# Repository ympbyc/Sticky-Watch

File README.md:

ISD1700 Fragmented Memory Manager
=================================

Arduino sketch that controls ISD1700 record/playback ic over SPI. It's packed with awesome features. Read on.

<!--  -->

Caution
-------

It's a WIP and a little buggy.

Features
--------

+ Fragmented memory management: divides the memory into N fixed-size randomly-accessible sections.
+ LED indicators: N LEDs can be attached to IO pins to indicate memory occupancy status and cursor position.
+ Multi-function buttons: Reduce the number of pushbuttons by utilizing single-click/double-click/long-press actions.
+ Sleep mode: Arduino enters SLEEP_MODE_PWR_DOWN after putting ISD1700 to power-down mode. Wakes up on button action and immediately executes the given command.

\* N being an integer

Default Setup
-------------

### Memory management

Address range is configured for ISD1790. Adjust LAST_ADDR macro value to match your chip. (Refer to ISD1700 Design Guide)

Number of sections the memory gets devided into is set by SLOT_NUM macro.

### APC register

By default the APC is setup to accept input from Mic. Change the APC macro value to match your need. (Refer to ISD1700 Design Guide)

### Push Buttons

#### MAIN_BTN

+ single-click: (play) play current section
+ long-press:   (rec)  start recording into first vacant section

#### SUB_BTN

+ single-click: forward
+ long-press:   erase current slot

### LEDs

+ ON when the section is occupied
+ OFF when the section is vacant
+ Blink to indicate current section (play, fwd, rec)

Default Wiring
--------------

| ISD1700 | Arduino |
| ------- | ------- |
| MISO    | D12     |
| MOSI    | D11     |
| SCLK    | D13     |
| SS      | D10     |

| Arduino | LED/BTN  |
| ------- | -------- |
| D14(A0) | LED0     |
| D15(A1) | LED1     |
| ...     | LEDN-1   |
| D3      | MAIN_BTN |
| D2      | SUB_BTN  |

Schematic
---------

<!--  -->

<!--  -->

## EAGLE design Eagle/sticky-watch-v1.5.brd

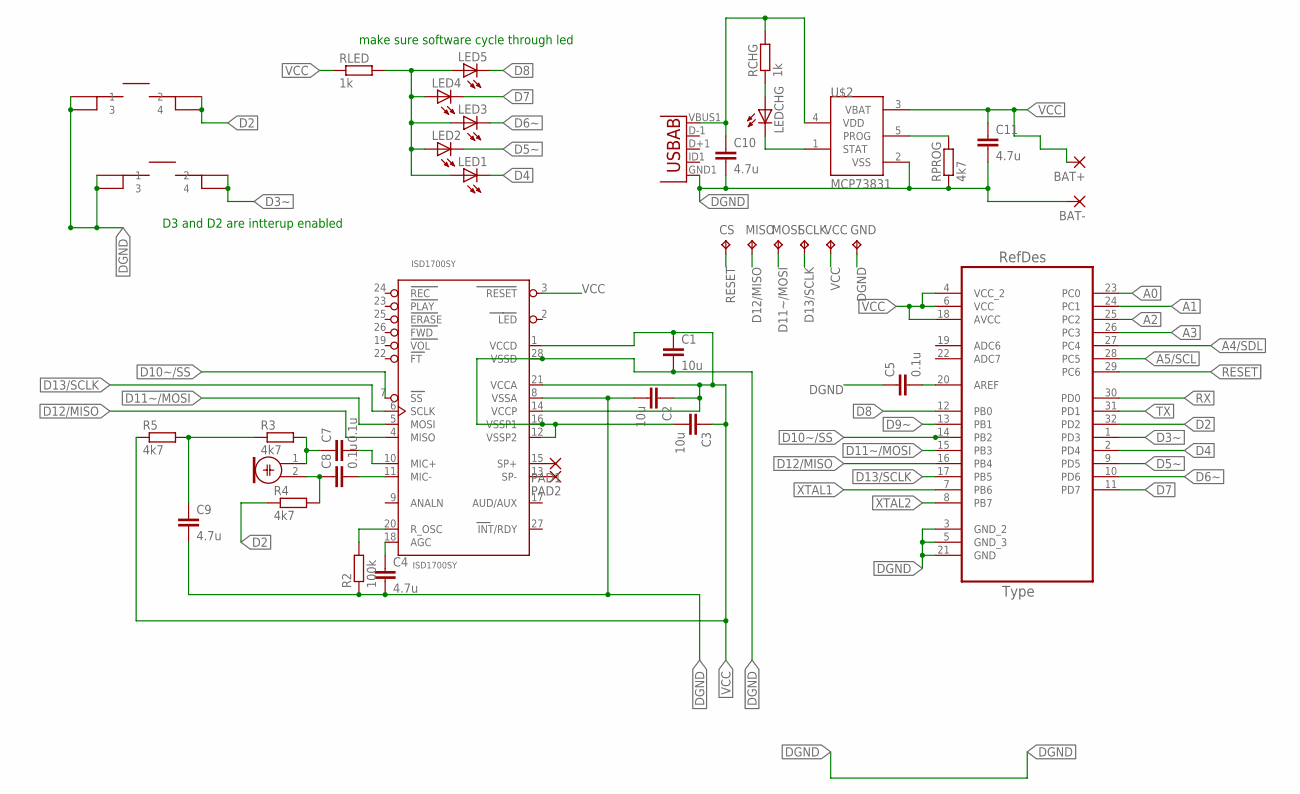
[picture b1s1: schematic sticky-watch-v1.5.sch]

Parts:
BAT+: 1,6/0,8
BAT-: 1,6/0,8
C1, C2, C3: 10u; C0603
C4, C9, C10, C11: 4.7u; C0603
C5, C7, C8: 0.1u; C0603
CS: TPTP10R; TP10R
GND: TPTP10R; TP10R
ISD1700SY: ISD1700SY; SO28W
LED1, LED2, LED3, LED4, LED5: LEDSML0805; SML0805
LEDCHG: LEDSML0805; SML0805
M1: ELECTRET_MICROPHON-WM-63PR; WM-63PR
MISO: TPTP10R; TP10R
MOSI: TPTP10R; TP10R
PAD1, PAD2: 1,6/0,8
R2: 100k; R0603
R3, R4, R5: 4k7; R0603
RCHG: 1k; R0603
RLED: 1k; R0603
RPROG: 4k7; R0603
S1: 0; SMD-TACT-5.2MM
S2: SMD-TACT; SMD-TACT-5.2MM
SCLK: TPTP10R; TP10R
U1: ATMEGA328P-AU; QFP80P900X900X120-32N
U2: USB""; USB-MICRO-SMD
U$2: MCP73831; SOT23-5L
VCC: TPTP10R; TP10R

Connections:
A0: U1.23 (PC0)
A1: U1.24 (PC1)
A2: U1.25 (PC2)
A3: U1.26 (PC3)
A4/SDL: U1.27 (PC4)
A5/SCL: U1.28 (PC5)
D2: R4.1, S2.2, S2.4, U1.32 (PD2)
D3~: S1.2, S1.4, U1.1 (PD3)
D4: LED1.C, U1.2 (PD4)
D5~: LED2.C, U1.9 (PD5)
D6~: LED3.C, U1.10 (PD6)
D7: LED4.C, U1.11 (PD7)
D8: LED5.C, U1.12 (PB0)
D9~: U1.13 (PB1)
D10~/SS: ISD1700SY.7 (SS), U1.14 (PB2)
D11~/MOSI: ISD1700SY.5 (MOSI), MOSI.TP, U1.15 (PB3)
D12/MISO: ISD1700SY.4 (MISO), MISO.TP, U1.16 (PB4)
D13/SCLK: ISD1700SY.6 (SCLK), SCLK.TP, U1.17 (PB5)
DGND: BAT-.1, C1.2, C2.2, C3.2, C4.2, C5.1, C9.2, C10.2, C11.2, GND.TP, ISD1700SY.8 (VSSA), ISD1700SY.12 (VSSP2), ISD1700SY.16 (VSSP1), ISD1700SY.28 (VSSD), R2.1, RPROG.1, S1.1, S1.3, S2.1, S2.3, U1.3 (GND_2), U1.5 (GND_3), U1.21 (GND), U2.GND1 (GND), U$2.2 (VSS)
unnamed: LED1.A, LED2.A, LED3.A, LED4.A, LED5.A, RLED.2
unnamed: C10.1, RCHG.2, U2.VBUS1 (VBUS), U$2.4 (VDD)
unnamed: ISD1700SY.15 (SP+), PAD1.1
unnamed: LEDCHG.A, RCHG.1
unnamed: C7.2, ISD1700SY.10 (MIC+)
unnamed: LEDCHG.C, U$2.1 (STAT)
unnamed: C5.2, U1.20 (AREF)
unnamed: ISD1700SY.13 (SP-), PAD2.1
unnamed: C4.1, ISD1700SY.18 (AGC)
unnamed: ISD1700SY.20 (R_OSC), R2.2
unnamed: C8.2, ISD1700SY.11 (MIC-)
unnamed: C8.1, M1.2, R4.2
unnamed: RPROG.2, U$2.5 (PROG)
unnamed: C9.1, R3.1, R5.2
unnamed: C7.1, M1.1, R3.2
RESET: CS.TP, U1.29 (PC6)
RX: U1.30 (PD0)
TX: U1.31 (PD1)
VCC: BAT+.1, C1.1, C2.1, C3.1, C11.1, ISD1700SY.1 (VCCD), ISD1700SY.3 (RESET), ISD1700SY.14 (VCCP), ISD1700SY.21 (VCCA), R5.1, RLED.1, U1.4 (VCC_2), U1.6 (VCC), U1.18 (AVCC), U$2.3 (VBAT), VCC.TP
XTAL1: U1.7 (PB6)
XTAL2: U1.8 (PB7)

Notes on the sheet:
make sure software cycle through led
D3 and D2 are intterup enabled

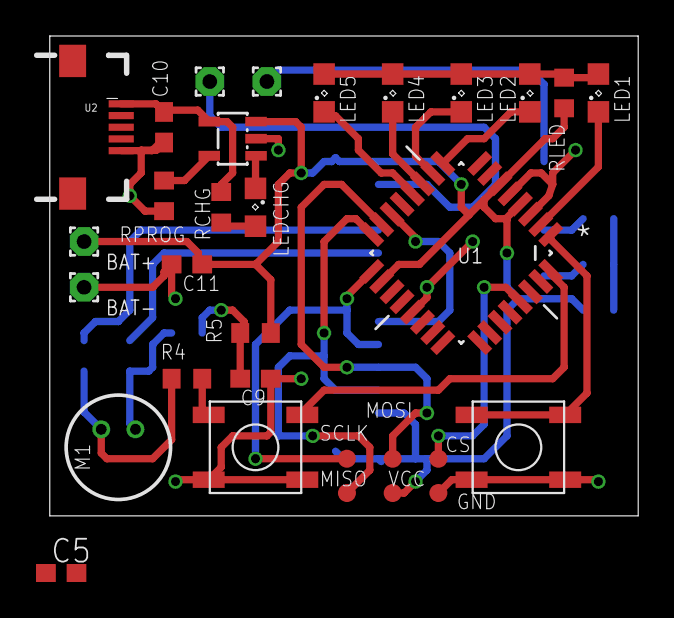
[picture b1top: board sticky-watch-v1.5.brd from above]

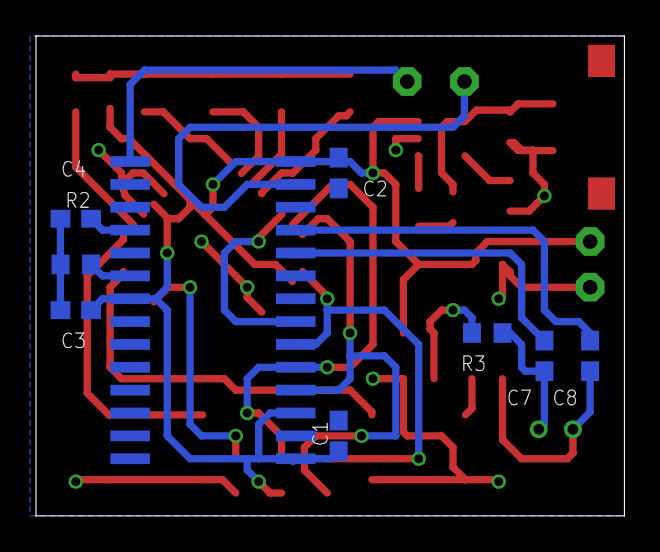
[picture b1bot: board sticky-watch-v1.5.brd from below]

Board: 2 copper layers, 32.7 x 26.7 mm, 40 parts (9 on the bottom side), 29 nets.

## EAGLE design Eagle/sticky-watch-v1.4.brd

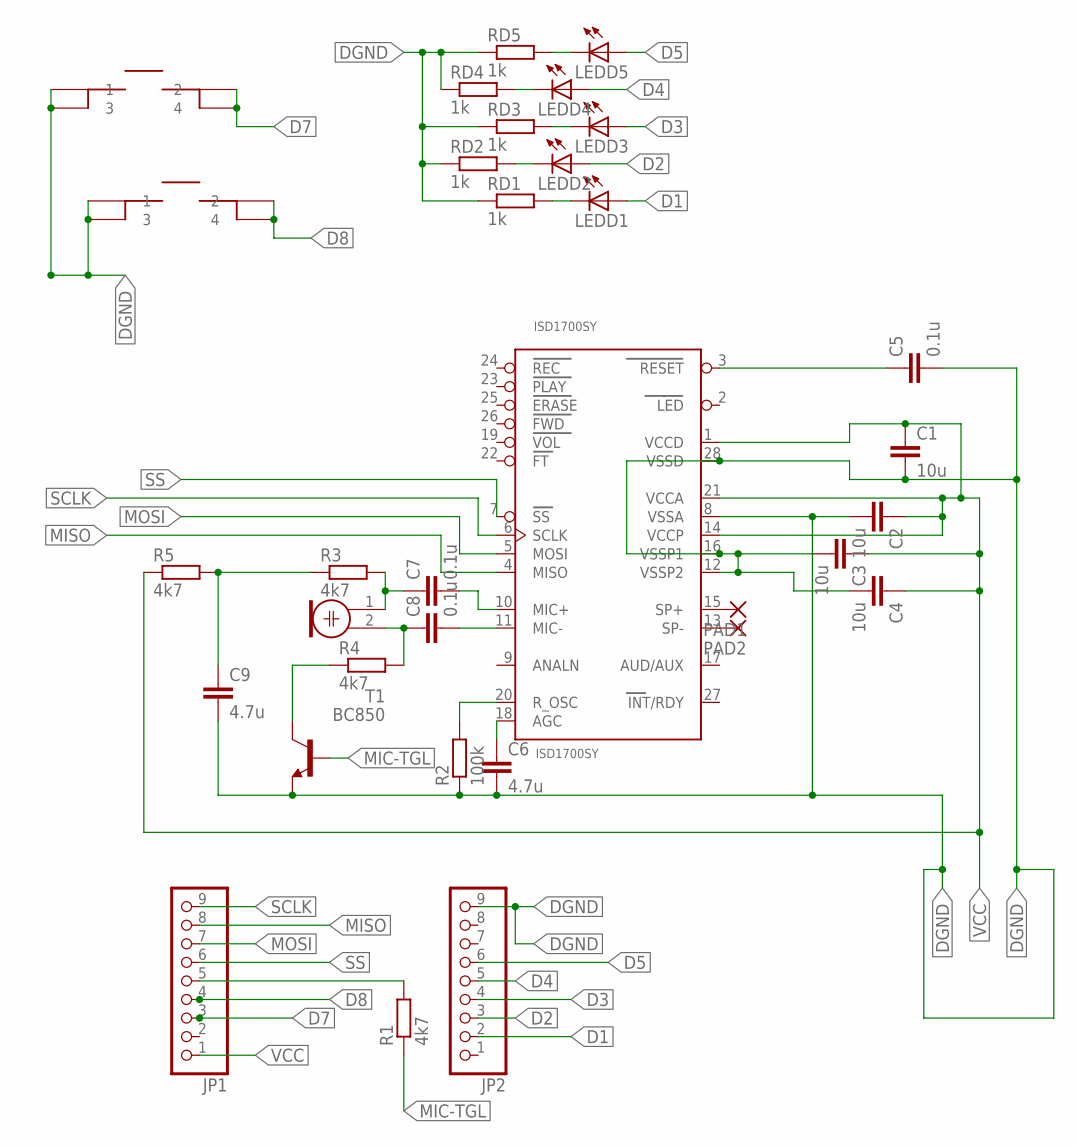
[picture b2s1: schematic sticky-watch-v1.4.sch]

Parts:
C1, C2, C3, C4: 10u; C0603
C5, C7, C8: 0.1u; C0603
C6, C9: 4.7u; C0603
ISD1700SY: ISD1700SY; SO28W
JP1, JP2: PINHD-1X9; 1X09
LEDD1, LEDD2, LEDD3, LEDD4, LEDD5: LEDSML0805; SML0805
M1: ELECTRET_MICROPHON-WM-63PR; WM-63PR
PAD1, PAD2: 1,6/0,8
R1, R3, R4, R5: 4k7; R0603
R2: 100k; R0603
RD1, RD2, RD3, RD4, RD5: 1k; R0603
S1: 0; SMD-TACT-5.2MM
S2: SMD-TACT; SMD-TACT-5.2MM
T1: BC850; SOT23

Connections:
D1: JP2.2, LEDD1.A
D2: JP2.3, LEDD2.A
D3: JP2.4, LEDD3.A
D4: JP2.5, LEDD4.A
D5: JP2.6, LEDD5.A
D7: JP1.3, S2.2, S2.4
D8: JP1.4, S1.2, S1.4
DGND: C1.2, C2.2, C3.2, C4.2, C5.2, C6.2, C9.2, ISD1700SY.8 (VSSA), ISD1700SY.12 (VSSP2), ISD1700SY.16 (VSSP1), ISD1700SY.28 (VSSD), JP2.9, R2.1, RD1.1, RD2.1, RD3.1, RD4.1, RD5.1, S1.1, S1.3, S2.1, S2.3, T1.2 (E)
MIC-TGL: R1.1, T1.1 (B)
MISO: ISD1700SY.4 (MISO), JP1.8
MOSI: ISD1700SY.5 (MOSI), JP1.7
unnamed: JP1.5, R1.2
unnamed: R4.1, T1.3 (C)
unnamed: ISD1700SY.15 (SP+), PAD1.1
unnamed: LEDD5.C, RD5.2
unnamed: C7.2, ISD1700SY.10 (MIC+)
unnamed: LEDD2.C, RD2.2
unnamed: LEDD3.C, RD3.2
unnamed: C5.1, ISD1700SY.3 (RESET)
unnamed: ISD1700SY.13 (SP-), PAD2.1
unnamed: C6.1, ISD1700SY.18 (AGC)
unnamed: ISD1700SY.20 (R_OSC), R2.2
unnamed: LEDD4.C, RD4.2
unnamed: C8.2, ISD1700SY.11 (MIC-)
unnamed: C8.1, M1.2, R4.2
unnamed: LEDD1.C, RD1.2
unnamed: C9.1, R3.1, R5.2
unnamed: C7.1, M1.1, R3.2
SCLK: ISD1700SY.6 (SCLK), JP1.9
SS: ISD1700SY.7 (SS), JP1.6
VCC: C1.1, C2.1, C3.1, C4.1, ISD1700SY.1 (VCCD), ISD1700SY.14 (VCCP), ISD1700SY.21 (VCCA), JP1.1, R5.1

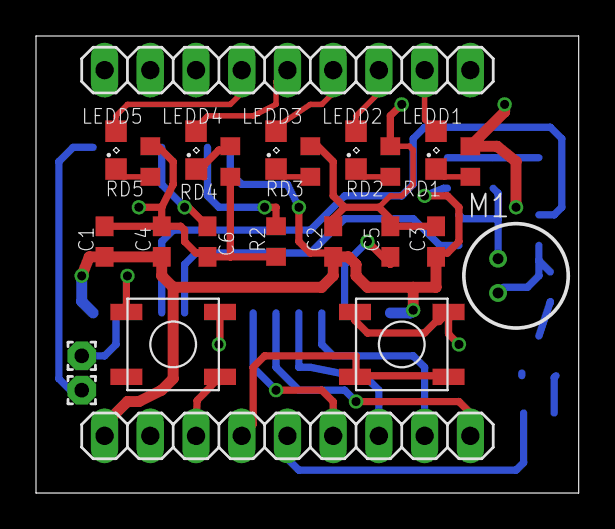
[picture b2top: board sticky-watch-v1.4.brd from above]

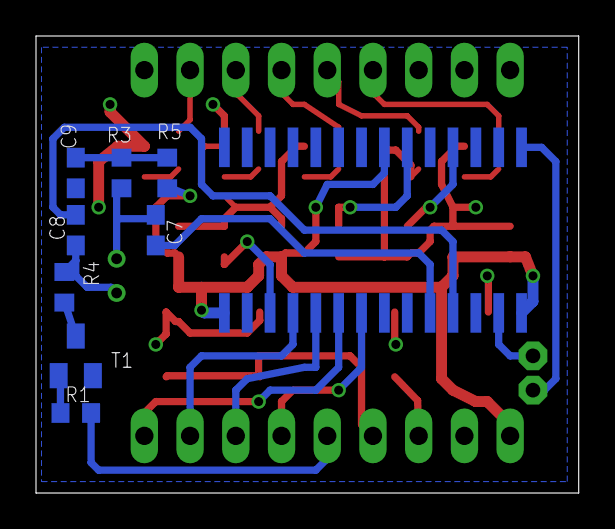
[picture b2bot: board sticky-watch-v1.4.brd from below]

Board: 2 copper layers, 30.2 x 25.4 mm, 33 parts (9 on the bottom side), 31 nets.

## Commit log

2017-05-22 v1.5 update. I'll followup with 3d models
